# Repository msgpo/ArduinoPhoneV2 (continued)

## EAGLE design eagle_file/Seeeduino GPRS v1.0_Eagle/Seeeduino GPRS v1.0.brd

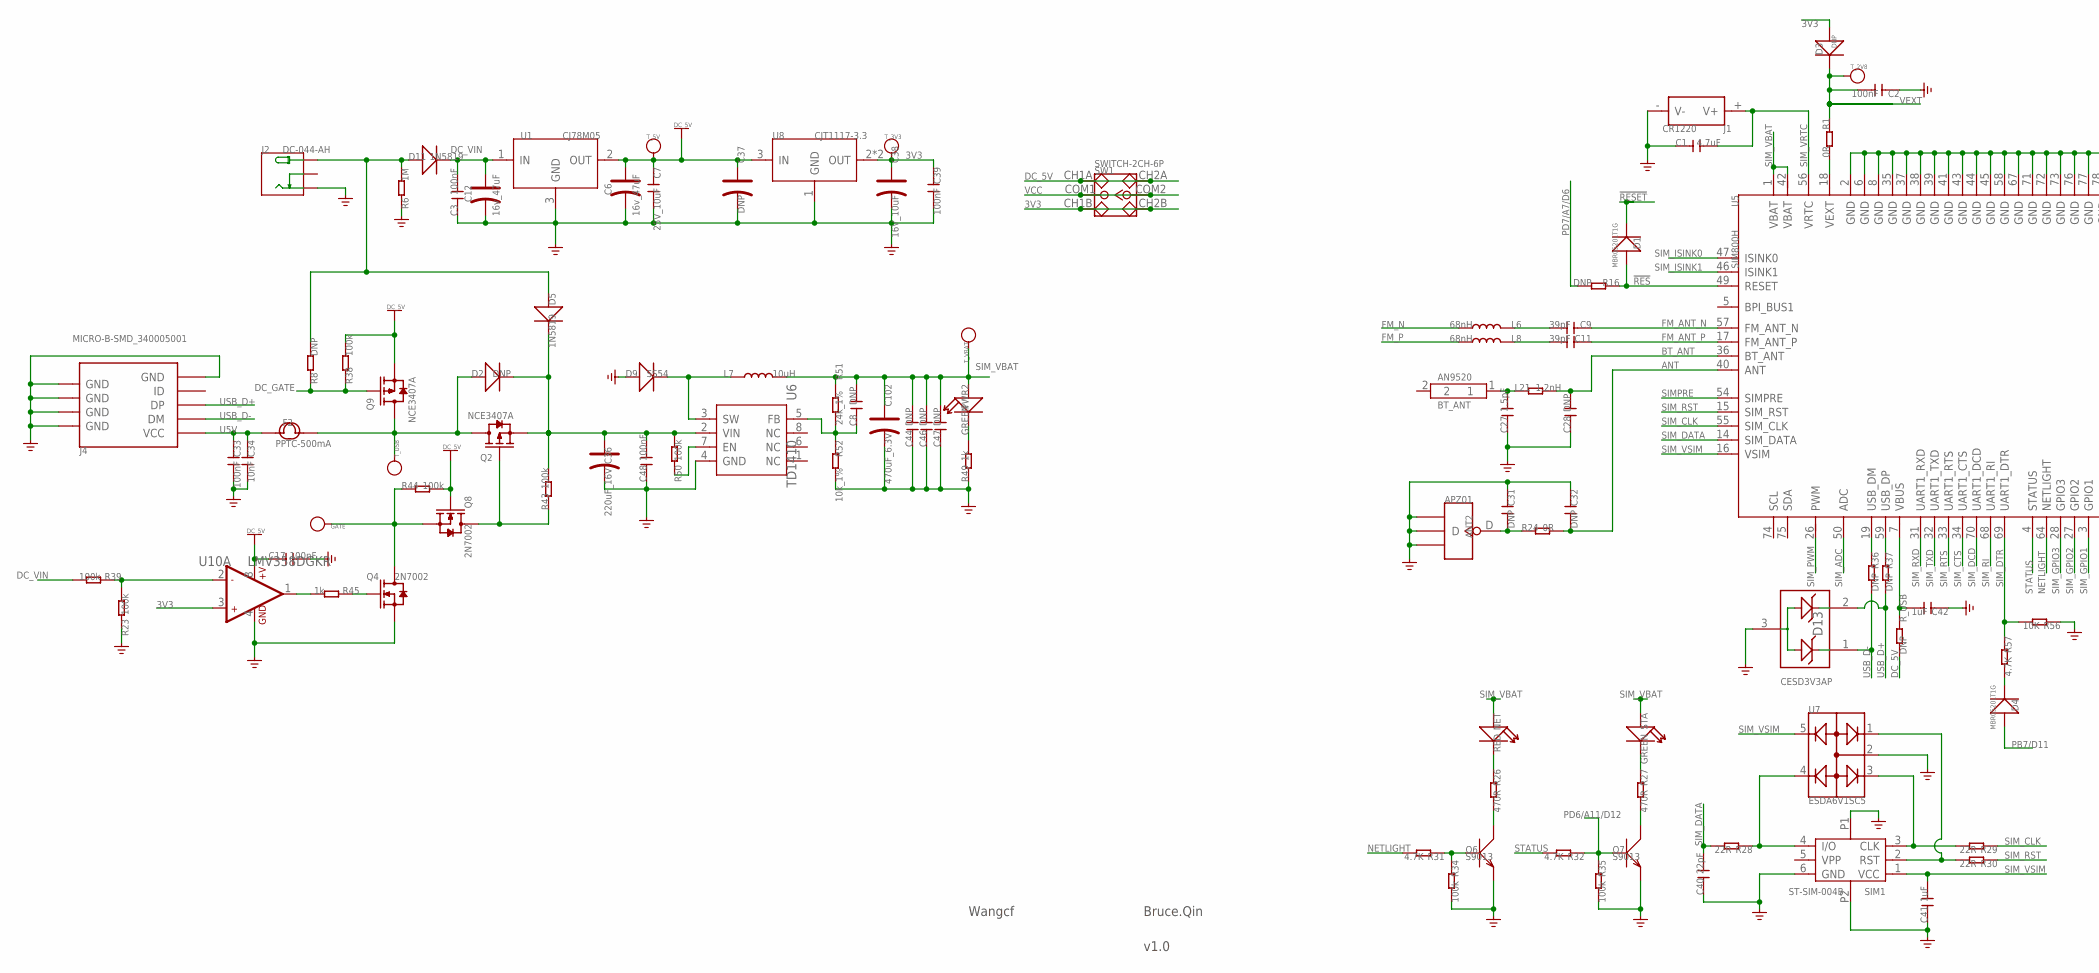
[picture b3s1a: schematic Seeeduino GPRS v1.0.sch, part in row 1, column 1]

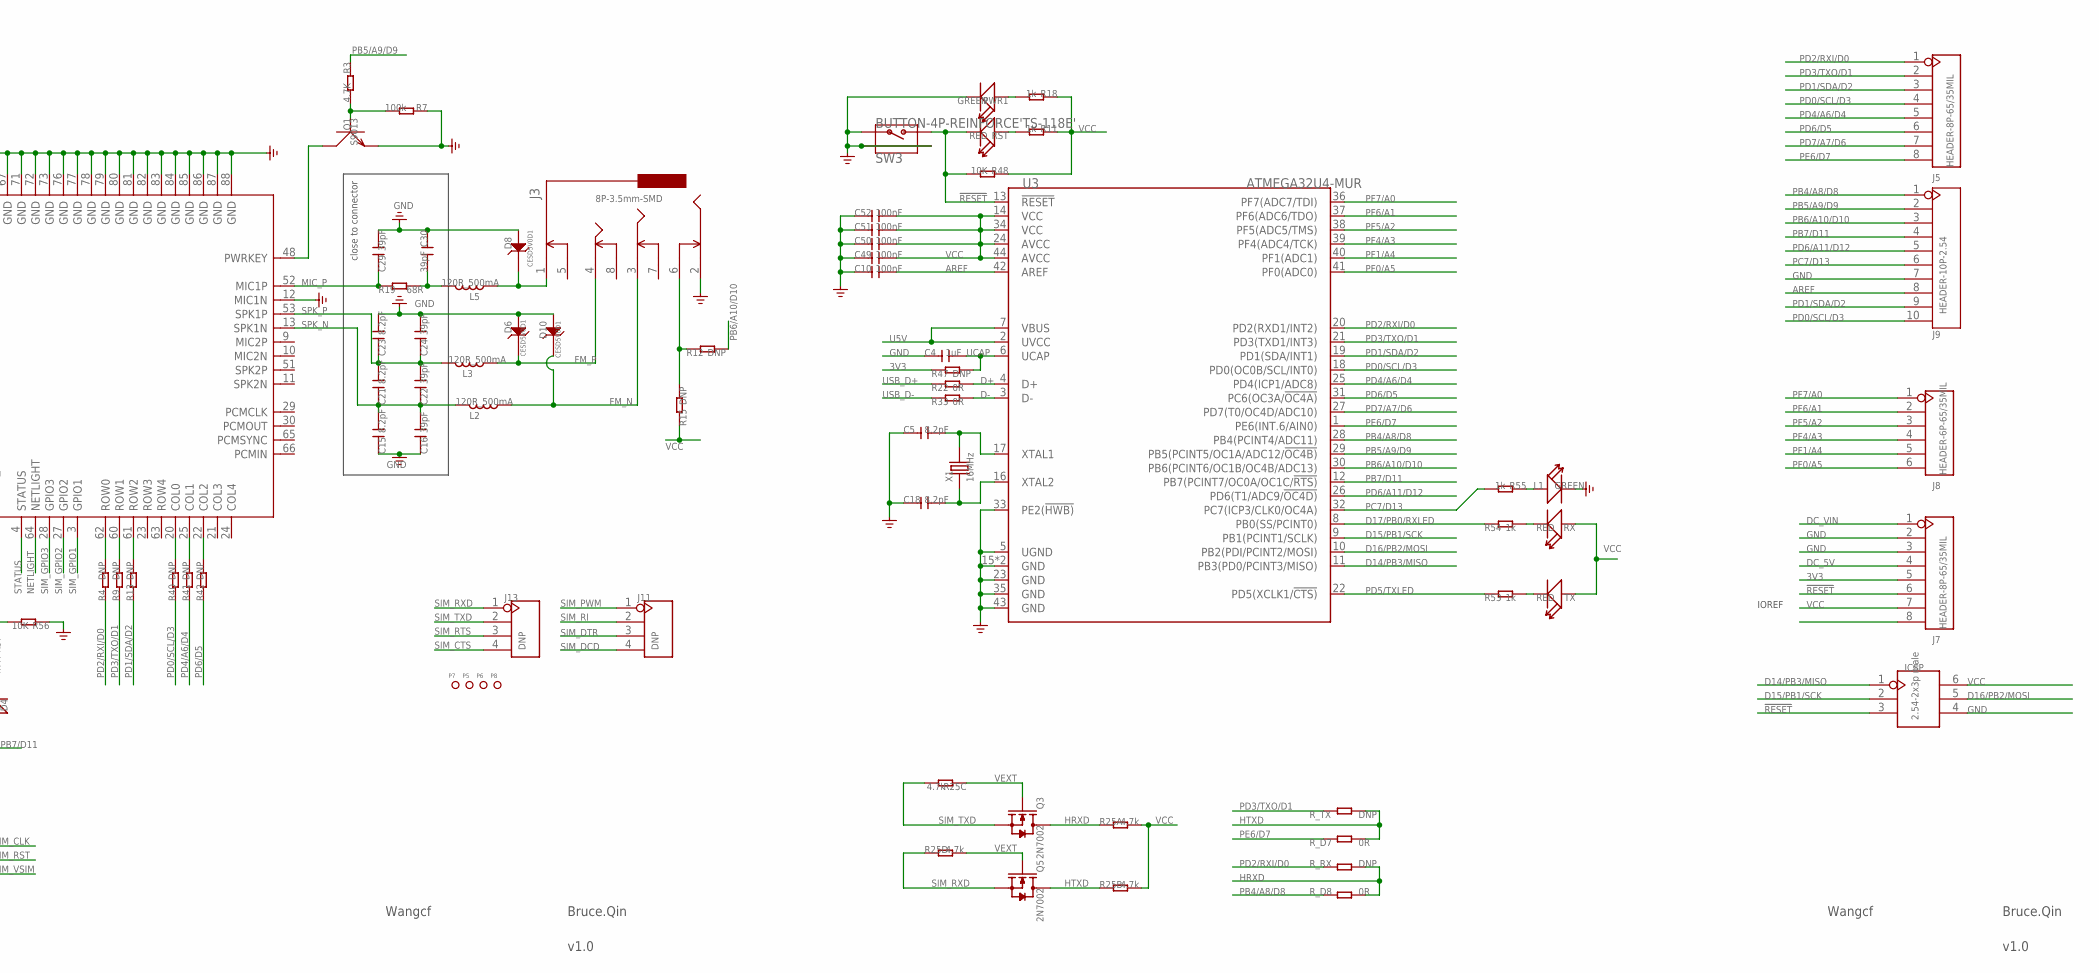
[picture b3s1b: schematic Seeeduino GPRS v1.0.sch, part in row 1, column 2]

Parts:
ANT2: APZ01; 4P-U-FL
BT_ANT: AN9520; 2P-9.5X2.1X1MM
C1: 4.7uF; C0805
C2, C3, C10, C17, C33, C39, C48, C49, C50, C51, C52: 100nF; C0603
C4, C41, C42: 1uF; C0603
C5, C15, C18, C21, C23: 8.2pF; C0603
C6, C12: 16v_47uF; AVX-C
C7: 25V_10uF; C0805
C8, C28, C31, C32, C44, C46, C47: DNP; C0603
C9, C11, C16, C22, C24, C29, C30: 39pF; C0603
C27: 1.5pF; C0603
C34: 10nF; C0603
C36: 220uF_16V; ELECTRO-SMD-D-5.6MM
C37: DNP; AVX-A
C38: 16V_10uF; AVX-A
C40: 22pF; C0603
C102: 470uF_6.3V; AVX-D
D1, D4: MBR0520LT1G; SOD123
D2: DNP; SMA
D3: DNP; SOD123
D5, D11: 1N5819; SMA
D6, D8, D10: CESD5V0D1; SOD123-2.7X1.6
D9: SS54; SMB
D13: CESD3V3AP; SOT23
F2: PPTC-500mA; 1206
GATE: DNP; TP_4545
ICSP: 2.54-2x3p male; 2X3P-2.54
J1: CR1220; SMD-CR1220-2
J2: DC-044-AH; DC-404
J3: 8P-3.5mm-SMD; 8P-3.5-SMD
J4: MICRO-B-SMD_340005001; MICRO-USB
J5, J7: HEADER-8P-65/35MIL; 8P-2.54-65/35MIL
J8: HEADER-6P-65/35MIL; 6P-2.54-65/35MIL
J9: HEADER-10P-2.54; 10P-2.54
J11, J13: DNP; 4P-65/35MIL
L1: GREEN; LED-0603
L2, L3, L5: 120R_500mA; L0603
L6, L8: 68nH; L0603
L7: 10uH; L0630
L21: 1.2nH; R0603
NET: RED; LED-0603
P5, P6, P7, P8: DNP; ROUND-MARK-1.0
PWR1, PWR2: GREEN; LED-0603
Q1, Q6, Q7: S9013; SOT23
Q2, Q9: NCE3407A; SOT23
Q3, Q4, Q5, Q8: 2N7002; SOT23
R1, R22, R24, R33: 0R; R0603
R3, R31, R32, R57: 4.7K; R0603
R4, R8, R9, R12, R13, R15, R16, R36, R37, R40, R41, R42, R47: DNP; R0603
R6: 1M; R0603
R7, R23, R34, R35, R38, R39, R43, R44, R50: 100k; R0603
R11, R18, R45, R49, R53, R54, R55: 1k; R0603
R19: 68R; R0603
R25: 4.7k; 1206-8-3.3X2.4
R26, R27: 470R; R0603
R28, R29, R30: 22R; R0603
R48, R56: 10K; R0603
R51: 24k_1%; R0603
R52: 10k_1%; R0603
RST: RED; LED-0603
RX: RED; LED-0603
R_D7, R_D8: 0R; R0603
R_RX: DNP; R0603
R_TX: DNP; R0603
R_USB: DNP; R0603
SIM1: ST-SIM-004B; 6P-1.8
STA: GREEN; LED-0603
SW1: SWITCH-2CH-6P; 6P-2CH-2.5-9.1X3.5X3.2H
SW3: BUTTON-4P-REINFORCE'TS-118E'; 4P-SMD-7X3.5X3.5H
TX: RED; LED-0603
T_2V8, T_3V3, T_5V: DNP; TP_4545
T_USB: DNP; TP_4545
T_VBAT: DNP; TP_4545
U1: CJ78M05; TO252
U3: ATMEGA32U4-MUR; QFN44
U5: SIM800H; 88P-17.8X15.8X2.4H
U6: TD1410; SOP8
U7: ESDA6V1SC5; SOT23-5L
U8: CJT1117-3.3; SOT-223
U10: LMV358DGKR; MSOP8
X1: 16MHz; 2P-SMD-5X3.2

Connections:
3V3: C38.+, C39.1, D3.+, J7.5, R47.1, SW1.CH1B, SW1.CH2B, T_3V3.T, U8.2 (OUT), U8.TER (OUT), U10.3 (+IN1)
!RES: D1.+, R16.1, U5.49 (RESET)
!RESET: D1.-, ICSP.3, J7.6, R48.2, RST.-, SW3.2, U3.13 (!RESET)
ANT: C32.2, R24.2, U5.40 (ANT)
AREF: C10.2, J9.8, U3.42 (AREF)
BT_ANT: C28.2, L21.2, U5.36 (BT_ANT)
D14/PB3/MISO: ICSP.1, U3.11 (PB3(PD0/PCINT3/MISO))
D15/PB1/SCK: ICSP.2, U3.9 (PB1(PCINT1/SCLK))
D16/PB2/MOSI: ICSP.5, U3.10 (PB2(PDI/PCINT2/MOSI))
D17/PB0/RXLED: R54.1, U3.8 (PB0(SS/PCINT0))
D+: R22.2, U3.4 (D+)
D-: R33.2, U3.3 (D-)
DC_5V: C6.+, C7.1, C17.1, C37.+, J7.4, Q8.1 (G), Q9.2 (S), R38.2, R44.2, R_USB.2, SW1.CH1A, SW1.CH2A, T_5V.T, U1.2 (OUT), U8.3 (IN), U10.8 (+V)
DC_GATE: GATE.T, Q4.3 (D), Q8.2 (S), Q9.1 (G), R8.1, R38.1, R44.1
DC_VIN: C3.2, C12.+, D11.1 (-), J7.1, R39.2, U1.1 (IN)
FM_ANT: D8.2, J3.1, L5.2
FM_ANT_N: C9.1, U5.57 (FM_ANT_N)
FM_ANT_P: C11.1, U5.17 (FM_ANT_P)
FM_N: D10.2, J3.3, L2.2, L6.2
FM_P: D6.2, J3.4, L3.2, L8.2
GND: ANT2.GND1, ANT2.GND2, ANT2.GND3, C1.1, C2.1, C3.1, C4.1, C5.1, C6.-, C7.2, C10.1, C12.-, C15.1, C16.1, C17.2, C18.1, C23.2, C24.2, C27.1, C28.1, C29.2, C30.1, C31.1, C32.1, C33.2, C34.2, C36.-, C37.-, C38.-, C39.2, C40.1, C41.1, C42.1, C44.1, C46.1, C47.1, C48.1, C49.1, C50.1, C51.1, C52.1, C102.-, D6.1, D8.1, D9.+, D10.1, D13.3, ICSP.4, J1.- (V-), J2.-, J3.2, J4.5 (GND), J4.S1 (GND), J4.S2 (GND), J4.S3 (GND), J4.S4 (GND), J4.S5 (GND), J4.S6 (GND), J7.2, J7.3, J9.7, L1.-, PWR1.-, Q1.2 (E), Q4.2 (S), Q6.2 (E), Q7.2 (E), R6.1, R7.1, R23.1, R34.2, R35.2, R49.1, R52.2, R56.1, SIM1.6 (GND), SIM1.P1 (7), SIM1.P2 (8), SW3.1, SW3.S1, SW3.S2, U1.3 (GND), U3.5 (UGND), U3.15 (GND), U3.23 (GND), U3.33 (PE2(!HWB)), U3.35 (GND), U3.43 (GND), U3.TAB (GND), U5.2 (GND), U5.6 (GND), U5.8 (GND), U5.12 (MIC1N), U5.35 (GND), U5.37 (GND), U5.38 (GND), U5.39 (GND), U5.41 (GND), U5.43 (GND), U5.44 (GND), U5.45 (GND), U5.58 (GND), U5.67 (GND), U5.71 (GND), U5.72 (GND), U5.73 (GND), U5.76 (GND), U5.77 (GND), U5.78 (GND), U5.79 (GND), U5.80 (GND), U5.81 (GND), U5.82 (GND), U5.83 (GND), U5.84 (GND), U5.85 (GND), U5.86 (GND), U5.87 (GND), U5.88 (GND), U6.4 (GND), U7.2, U8.1 (GND), U10.4 (GND)
HRXD: Q3.3 (D), R25.1, R_D8.2, R_RX.2
HTXD: Q5.3 (D), R25.2 (1), R_D7.2, R_TX.2
I/O: R28.1, SIM1.4 (I/O), U7.4
MIC_P: C29.1, R19.1, U5.52 (MIC1P)
unnamed: Q6.1 (B), R31.1, R34.1
unnamed: Q6.3 (C), R26.2
unnamed: D4.-, R57.2
unnamed: R1.2, U5.18 (VEXT)
unnamed: R23.2, R39.1, U10.2 (-IN1)
unnamed: J3.6, R12.1, R15.2
unnamed: R36.1, U5.19 (USB_DM)
unnamed: C11.2, L8.1
unnamed: Q1.1 (B), R3.2, R7.2
unnamed: C9.2, L6.1
unnamed: R30.2, SIM1.2 (RST), U7.1
unnamed: R29.2, SIM1.3 (CLK), U7.3
unnamed: R11.2, RST.+
unnamed: R37.1, U5.59 (USB_DP)
unnamed: D2.2 (+), F2.2, Q2.3 (D), Q9.3 (D), T_USB.T
unnamed: C42.2, R_USB.1, U5.7 (VBUS)
unnamed: R4.2, U5.62 (ROW0)
unnamed: R9.2, U5.60 (ROW1)
unnamed: R13.2, U5.61 (ROW2)
unnamed: D5.2 (+), D11.2 (+), J2.+, R6.2, R8.2
unnamed: R45.2, U10.1 (OUT1)
unnamed: NET.-, R26.1
unnamed: C30.2, L5.1, R19.2
unnamed: PWR1.+, R18.2
unnamed: R40.2, U5.20 (COL0)
unnamed: R41.2, U5.25 (COL1)
unnamed: R42.2, U5.22 (COL2)
unnamed: Q2.1 (G), Q8.3 (D), R43.1
unnamed: Q4.1 (G), R45.1
unnamed: C5.2, U3.17 (XTAL1), X1.2
unnamed: PWR2.-, R49.2
unnamed: R50.1, U6.7 (EN)
unnamed: C18.2, U3.16 (XTAL2), X1.1
unnamed: R53.2, TX.-
unnamed: C36.+, C48.2, D2.1 (-), D5.1 (-), Q2.2 (S), R43.2, R50.2, U6.2 (VIN)
unnamed: C8.1, R51.2, R52.1, U6.5 (FB)
unnamed: D9.-, L7.1, U6.3 (SW)
unnamed: R54.2, RX.-
unnamed: L1.+, R55.1
unnamed: Q7.3 (C), R27.2
unnamed: R27.1, STA.-
unnamed: BT_ANT.1, C27.2, L21.1
unnamed: ANT2.D, C31.2, R24.1
NETLIGHT: R31.2, U5.64 (NETLIGHT)
PB4/A8/D8: J9.1, R_D8.1, U3.28 (PB4(PCINT4/ADC11))
PB5/A9/D9: J9.2, R3.1, U3.29 (PB5(PCINT5/OC1A/ADC12/!OC4B))
PB6/A10/D10: J9.3, R12.2, U3.30 (PB6(PCINT6/OC1B/OC4B/ADC13))
PB7/D11: D4.+, J9.4, U3.12 (PB7(PCINT7/OC0A/OC1C/!RTS))
PC7/D13: J9.6, R55.2, U3.32 (PC7(ICP3/CLK0/OC4A))
PD0/SCL/D3: J5.4, J9.10, R40.1, U3.18 (PD0(OC0B/SCL/INT0))
PD1/SDA/D2: J5.3, J9.9, R13.1, U3.19 (PD1(SDA/INT1))
PD2/RXI/D0: J5.1, R4.1, R_RX.1, U3.20 (PD2(RXD1/INT2))
PD3/TXO/D1: J5.2, R9.1, R_TX.1, U3.21 (PD3(TXD1/INT3))
PD4/A6/D4: J5.5, R41.1, U3.25 (PD4(ICP1/ADC8))
PD5/TXLED: R53.1, U3.22 (PD5(XCLK1/!CTS))
PD6/A11/D12: J9.5, Q7.1 (B), R32.1, R35.1, U3.26 (PD6(T1/ADC9/!OC4D))
PD6/D5: J5.6, R42.1, U3.31 (PC6(OC3A/!OC4A))
PD7/A7/D6: J5.7, R16.2, U3.27 (PD7(T0/OC4D/ADC10))
PE6/D7: J5.8, R_D7.1, U3.1 (PE6(INT.6/AIN0))
PF0/A5: J8.6, U3.41 (PF0(ADC0))
PF1/A4: J8.5, U3.40 (PF1(ADC1))
PF4/A3: J8.4, U3.39 (PF4(ADC4/TCK))
PF5/A2: J8.3, U3.38 (PF5(ADC5/TMS))
PF6/A1: J8.2, U3.37 (PF6(ADC6/TDO))
PF7/A0: J8.1, U3.36 (PF7(ADC7/TDI))
PWRKEY: Q1.3 (C), U5.48 (PWRKEY)
SIMPRE: U5.54 (SIMPRE)
SIM_ADC: U5.50 (ADC)
SIM_CLK: R29.1, U5.55 (SIM_CLK)
SIM_CTS: J13.4, U5.34 (UART1_CTS)
SIM_DATA: C40.2, R28.2, U5.14 (SIM_DATA)
SIM_DCD: J11.4, U5.70 (UART1_DCD)
SIM_DTR: J11.3, R56.2, R57.1, U5.69 (UART1_DTR)
SIM_GPIO1: U5.3 (GPIO1)
SIM_GPIO2: U5.27 (GPIO2)
SIM_GPIO3: U5.28 (GPIO3)
SIM_ISINK0: U5.47 (ISINK0)
SIM_ISINK1: U5.46 (ISINK1)
SIM_PWM: J11.1, U5.26 (PWM)
SIM_RI: J11.2, U5.68 (UART1_RI)
SIM_RST: R30.1, U5.15 (SIM_RST)
SIM_RTS: J13.3, U5.33 (UART1_RTS)
SIM_RXD: J13.1, Q5.2 (S), R25.4 (1), U5.31 (UART1_RXD)
SIM_TXD: J13.2, Q3.2 (S), R25.6 (2), U5.32 (UART1_TXD)
SIM_VBAT: C8.2, C44.2, C46.2, C47.2, C102.+, L7.2, NET.+, PWR2.+, R51.1, STA.+, T_VBAT.T, U5.1 (VBAT), U5.42 (VBAT)
SIM_VRTC: C1.2, J1.+ (V+), U5.56 (VRTC)
SIM_VSIM: C41.2, SIM1.1 (VCC), U5.16 (VSIM), U7.5
SPK_N: C15.2, C16.2, C21.1, C22.1, L2.1, U5.13 (SPK1N)
SPK_P: C21.2, C22.2, C23.1, C24.1, L3.1, U5.53 (SPK1P)
STATUS: R32.2, U5.4 (STATUS)
U5V: C33.1, C34.1, F2.1, J4.1 (VCC), U3.2 (UVCC), U3.7 (VBUS)
UCAP: C4.2, R47.2, U3.6 (UCAP)
USB_D+: D13.2, J4.3 (DP), R22.1, R37.2
USB_D-: D13.1, J4.2 (DM), R33.1, R36.2
VCC: C49.2, C50.2, C51.2, C52.2, ICSP.6, J7.7, R11.1, R15.1, R18.1, R25.7 (2), R25.8 (2), R48.1, RX.+, SW1.COM1, SW1.COM2, TX.+, U3.14 (VCC), U3.24 (AVCC), U3.34 (VCC), U3.44 (AVCC)
VEXT: C2.2, D3.-, Q3.1 (G), Q5.1 (G), R1.1, R25.3 (1), R25.5 (2), T_2V8.T

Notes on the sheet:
Wangcf
v1.0
Bruce.Qin
close to connector
IOREF

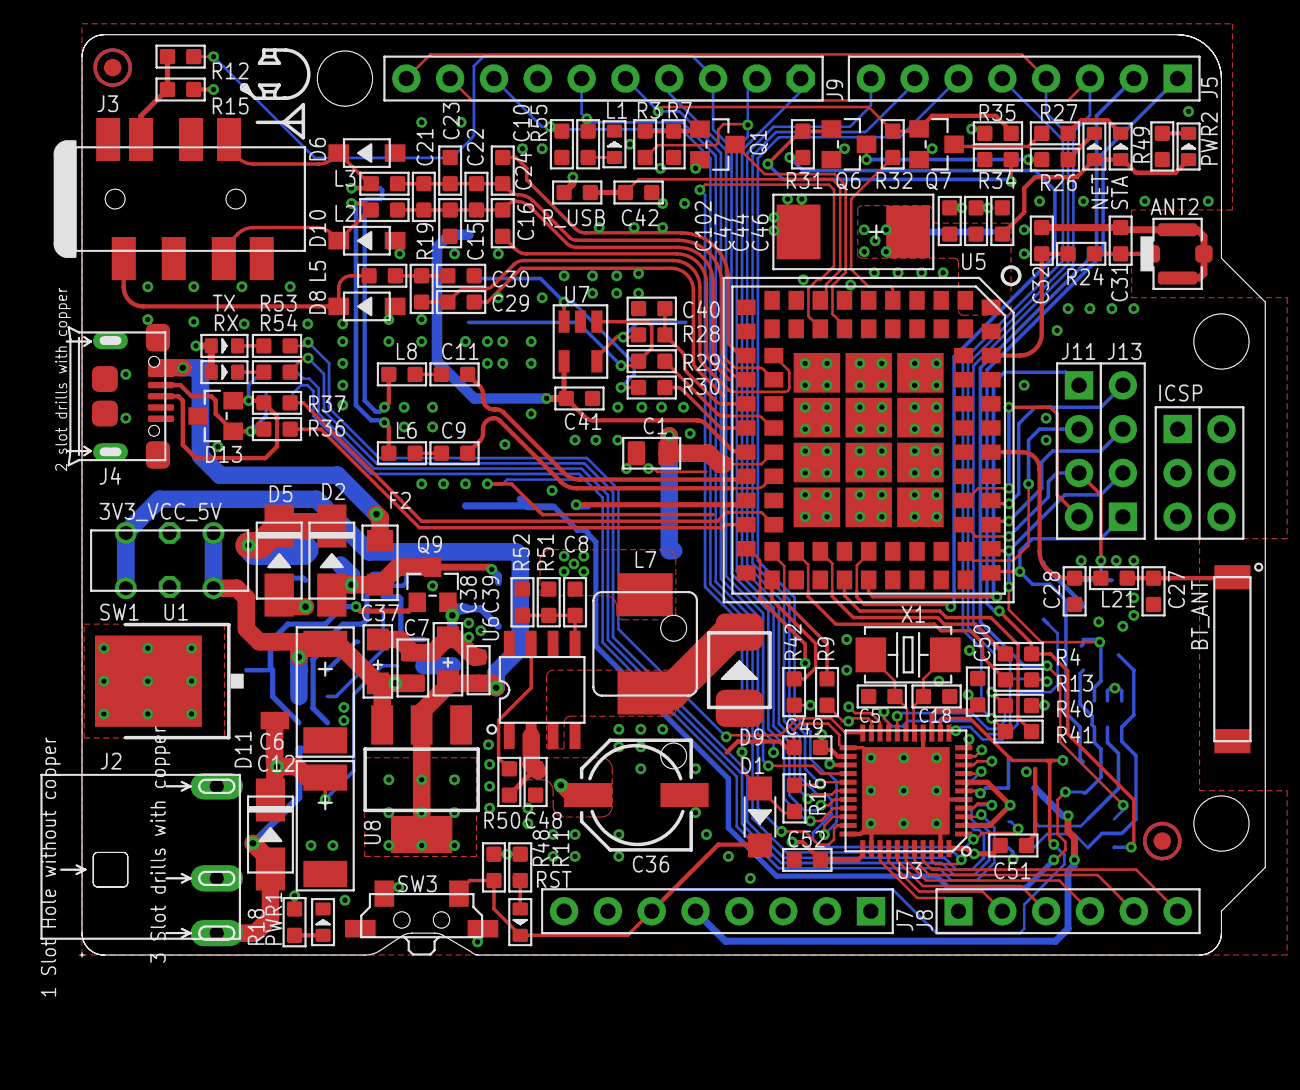
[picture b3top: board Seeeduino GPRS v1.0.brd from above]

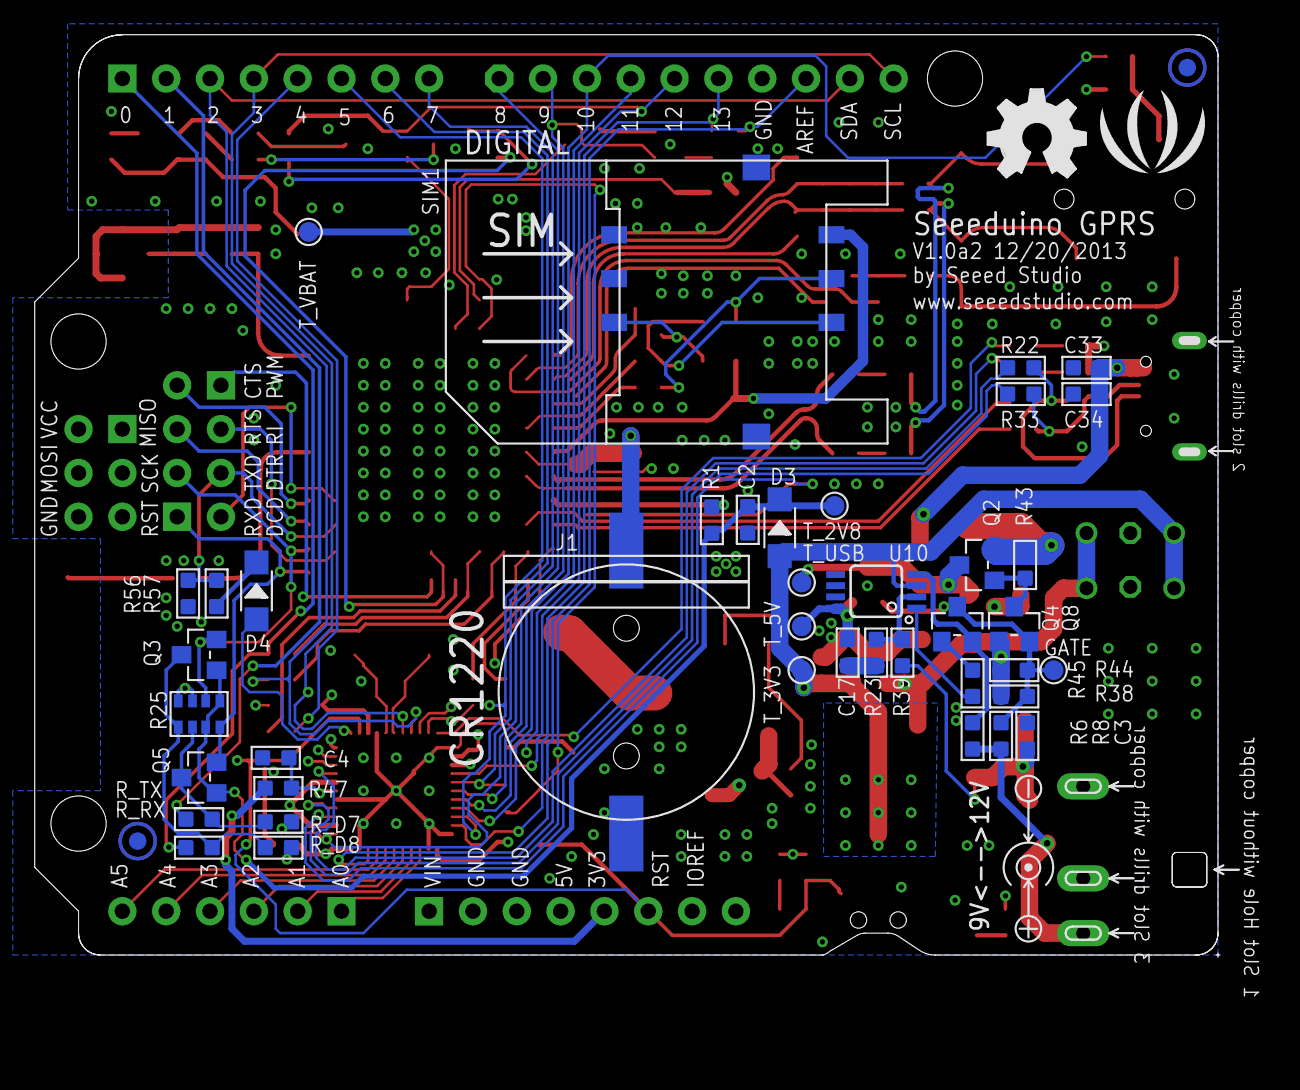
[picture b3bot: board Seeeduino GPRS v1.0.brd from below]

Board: 4 copper layers, 69.8 x 53.5 mm, 170 parts (45 on the bottom side), 114 nets.

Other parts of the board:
U$36: LOGO_SILK
U$42: OSHW_FILLX200_NOTEXT

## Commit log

2016-01-25 first sygn
2016-02-15 add button
